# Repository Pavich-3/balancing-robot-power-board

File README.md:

# balancing-robot-power-board
Power board for self-balancing robot with dual DRV8871 motor drivers and MPU-6050 IMU
## Preview

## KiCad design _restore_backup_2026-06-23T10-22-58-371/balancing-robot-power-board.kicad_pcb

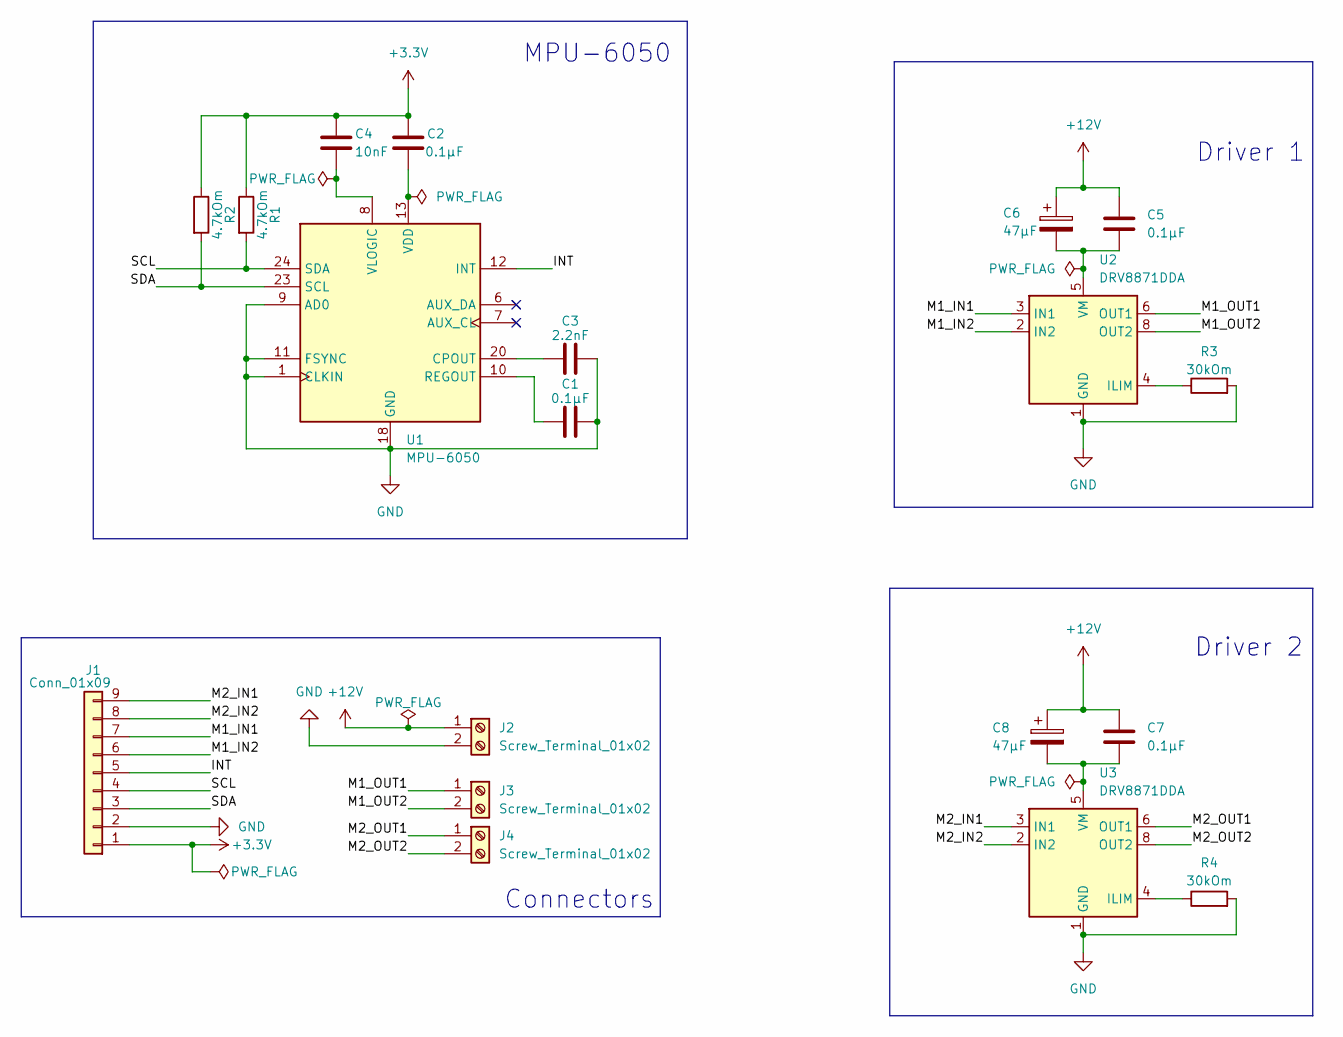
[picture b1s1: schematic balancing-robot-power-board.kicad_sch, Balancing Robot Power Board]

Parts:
C1, C2, C5, C7: 0.1µF; C_0603_1608Metric
C3: 2.2nF; C_0603_1608Metric
C4: 10nF; C_0603_1608Metric
C6, C8: 47µF; CP_Elec_6.3x7.7
J1: Conn_01x09; PinSocket_1x09_P2.54mm_Vertical
J2, J3, J4: Screw_Terminal_01x02; TerminalBlock_Xinya_XY308-2.54-2P_1x02_P2.54mm_Horizontal
R1, R2: 4.7kOm; R_0603_1608Metric
R3, R4: 30kOm; R_0603_1608Metric
U1: MPU-6050; InvenSense_QFN-24_4x4mm_P0.5mm
U2, U3: DRV8871DDA; Texas_HTSOP-8-1EP_3.9x4.9mm_P1.27mm_EP2.95x4.9mm_Mask2.4x3.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

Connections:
+3.3V: C2.1, C4.1, J1.1, R1.1, R2.1
+12V: C5.1, C6.1, C7.1, C8.1, J2.1
/INT: J1.5, U1.12 (INT)
/M1_IN1: J1.7, U2.3 (IN1)
/M1_IN2: J1.6, U2.2 (IN2)
/M1_OUT1: J3.1, U2.6 (OUT1)
/M1_OUT2: J3.2, U2.8 (OUT2)
/M2_IN1: J1.9, U3.3 (IN1)
/M2_IN2: J1.8, U3.2 (IN2)
/M2_OUT1: J4.1, U3.6 (OUT1)
/M2_OUT2: J4.2, U3.8 (OUT2)
/SCL: J1.4, R1.2, U1.24 (SDA)
/SDA: J1.3, R2.2, U1.23 (SCL)
GND: C1.2, C3.2, J1.2, J2.2, R3.2, R4.2, U1.1 (CLKIN), U1.9 (AD0), U1.11 (FSYNC), U1.18 (GND), U2.1 (GND), U2.7 (GND), U2.9 (GND), U3.1 (GND), U3.7 (GND), U3.9 (GND)
unnamed: C3.1, U1.20 (CPOUT)
unnamed: C1.1, U1.10 (REGOUT)
unnamed: C2.2, U1.13 (VDD)
unnamed: C4.2, U1.8 (VLOGIC)
unnamed: R3.1, U2.4 (ILIM)
unnamed: C5.2, C6.2, U2.5 (VM)
unnamed: R4.1, U3.4 (ILIM)
unnamed: C7.2, C8.2, U3.5 (VM)

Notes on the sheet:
MPU-6050
Connectors
Driver 2
Driver 1

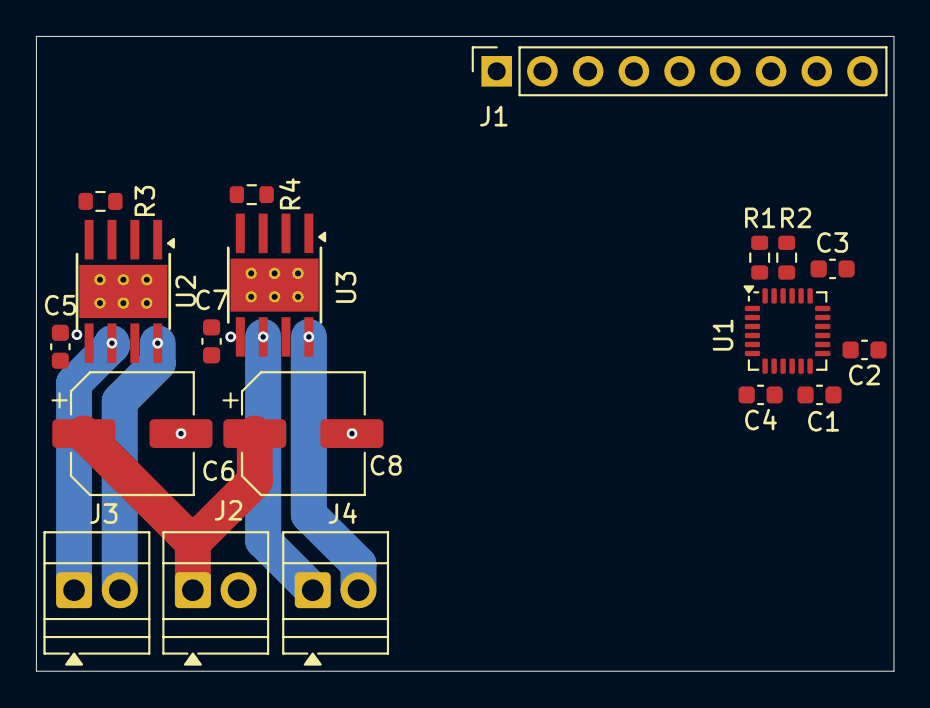
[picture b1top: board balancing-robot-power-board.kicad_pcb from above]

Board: 2 copper layers, 47.6 x 35.3 mm, 19 parts (0 on the bottom side), 22 nets.

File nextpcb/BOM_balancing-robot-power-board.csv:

Designator,Quantity,MPN,manufacturer,Package/Footprint,Description,Procurement Type,Customer Note
C3,1,,,C_0603_1608Metric,2.2nF,,
C4,1,,,C_0603_1608Metric,10nF,,
"C5,C1,C7,C2",4,,,C_0603_1608Metric,0.1µF,,
"C8,C6",2,,,CP_Elec_6.3x7.7,47µF,,
J1,1,,,PinSocket_1x09_P2.54mm_Vertical,Conn_01x09,,
"J4,J2,J3",3,,,TerminalBlock_Xinya_XY308-2.54-2P_1x02_P2.54mm_Horizontal,Screw_Terminal_01x02,,
"R2,R1",2,,,R_0603_1608Metric,4.7kOm,,
"R4,R3",2,,,R_0603_1608Metric,30kOm,,
U1,1,,,InvenSense_QFN-24_4x4mm_P0.5mm,MPU-6050,,
"U3,U2",2,,,Texas_HTSOP-8-1EP_3.9x4.9mm_P1.27mm_EP2.95x4.9mm_Mask2.4x3.1mm_ThermalVias,DRV8871DDA,,

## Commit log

2026-06-26 Initial KiCad PCB design
2026-06-26 Update .gitignore to include additional file types
    Add various file types to .gitignore for project cleanliness.
2026-06-26 Clean up repository
2026-06-26 Remove lock and generated files
2026-06-26 Remove KiCad local history
2026-06-26 Add project preview images
2026-06-26 Fix image path for 3D Bottom in README
